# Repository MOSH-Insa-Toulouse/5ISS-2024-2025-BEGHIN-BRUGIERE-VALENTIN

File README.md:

# Gaz Sensor Application

## Introduction
The general objective of this project is to carry out the complete implementation of a gas sensor, from its manufacture, through its integration on a PCB, to its use in a concrete IoT application. This course gives us the opportunity to put our skills into practice at every stage in the design and development of a project. In particular, it covers the main phases such as hardware design, software design and product integration. Various digital tools were used, including KiCad for PCB design, LTSpice for analogue simulations and the Arduino platform for programming.

The application developed detects carbon monoxide and alerts you if critical thresholds are exceeded. Three LEDs indicate the alert levels: green for a safe level, orange for a high level and red for a dangerous level requiring evacuation. An OLED screen, connected via I2C, displays CO levels in real time to check the accuracy of the measurements. These measurements are then sent via a LoRa antenna and retrieved using the NodeRed software, which displays them.

This Git file and the following document contain the steps required to design our application, as well as the results obtained.

## LoRa Antenna
As mentioned above, the aim is to send the data measured by the sensor via a LoRa antenna. To do this, we used the open-source LoRaWAN Network Server ChirpStack, on which we created our application and generated its identifier and access key. Via this server, it is possible to connect to the GEI's main LoRa antenna and view the data stream sent to it.

On the programming side, we used the LoRa RN2483. This module has the advantage of communicating via the UART, so it was easy to connect it to the Arduino and have it send and receive data. We then had to reset and configure the RN2483 microchip according to the identifiers created on ChirpStack. Once this was done, we launched the connection tests and were able to check that our antenna was indeed connected to the main antenna via ChirpStack.

## Components Integration
### OLED Screen
As already mentioned, the OLED screen displays the carbon monoxide level measured by the sensor. The display is of the SSD1306 type and communicates via the I2C bus. We were therefore able to integrate it easily into our system, in particular by using adafruit libraries. By configuring the screen display, i.e. the size, colour and position of the text, we were able to display our first tests on the screen. We also used this screen as a test indicator to check the veracity and accuracy of the measurements taken by the sensor.
### Gaz Sensor
Adding the gas sensor to the application was not so easy. We had trouble understanding how the sensor worked and how to retrieve the measurements. However, after a bit of research we managed to get it to work properly.

This sensor detects the presence of carbon monoxide by a variation in resistance. First of all, the sensor has to be allowed to heat up in order to obtain values in line with reality, and then to adapt to its environment. The resistance value is recovered via a serial link and processed to obtain a usable level in ppm. We were then able to display on the screen the measurements taken in real time by the sensor.
### LEDs
To implement a visual alert, we decided to use three different coloured LEDs to symbolise our alert levels. The first level, green, means that the level of CO measured by the sensor is not toxic. The second, orange, symbolises that the quantity of gas is high and that exposure for too long can cause headaches. Finally, the red alert level lights up when the level of monoxide is above the safety threshold. Time to leave the room. We found the three thresholds in the literature on the websites of health bodies to reflect reality. The LEDs were switched on via a condition loop when the sensor measurements were retrieved.

## Node-RED Application
After that, we implemented Node-RED to visualise the data collected by the sensor. The idea was for the sensor readings transmitted via the LoRa antenna and processed by Chirpstack to be retrieved by Node-RED and displayed using its dashboard functionality. Using the MQTT protocol, we subscribed Node-RED to a Chirpstack topic in which it published the sensor measurements. This enabled us to retrieve the data transmitted on the LoRa network. The values were then displayed by creating a simple but powerful interface for viewing the gas sensor data in real time. 

For more information, read the Node-RED report [here](Rapport_NodeRed).

## The electrical circuit
Here is the complete electrical diagram of our system. It consists of the Arduino UNO shield, the three LEDs, the gas sensor, the OLED screen and an amplifier.

The gas sensor produced has a very high resistance which varies according to the type and presence of gas. Its resistance is of the order of gigohms, which implies an extremely low current of the order of nanoampere (nA) flowing to the ADC. Using an Arduino with a 10-bit ADC requires the signal leaving the gas sensor to be amplified. We therefore designed an amplification circuit based on an operational amplifier and simulated it using LTSpice. To find out more, read the LT-Spice report [here](Rapport_LTSpice).

## PCB Design
The PCB was designed using KiCad software. Starting with the previous electrical circuit, the components had to be placed on the Arduino UNO shield and then routed. This was a complex process because we had a lot of components that were quite imposing in terms of space, which did not make placement easy. The final aim was, instead of using a breadboard, to have all the components needed for our application on a single board. The OLED screen and the connectors for the LoRa module have been placed on the other side of the shield so that they can be accessed. Here is the final PCB for our project.

Below, there is a 3D view of the PCB after conception.

-- Front view:

--Back view:

## Conclusion
The next stage of our project is to print the PCB and then solder the components. Finally, we will have to test our application by uploading our code onto the board. 

The overall objective of this module is to carry out the complete implementation of a gas sensor, from its manufacture, through its integration on a PCB, to its use in a concrete IoT application. This course thus gives us the opportunity to put our skills into practice at every stage of the design and development of a project. In particular, it covers the main phases such as hardware design, software design and product integration. 

In terms of energy consumption, we should look at the consumption of each component. If it is too high, we will have to switch to other components that consume less energy.

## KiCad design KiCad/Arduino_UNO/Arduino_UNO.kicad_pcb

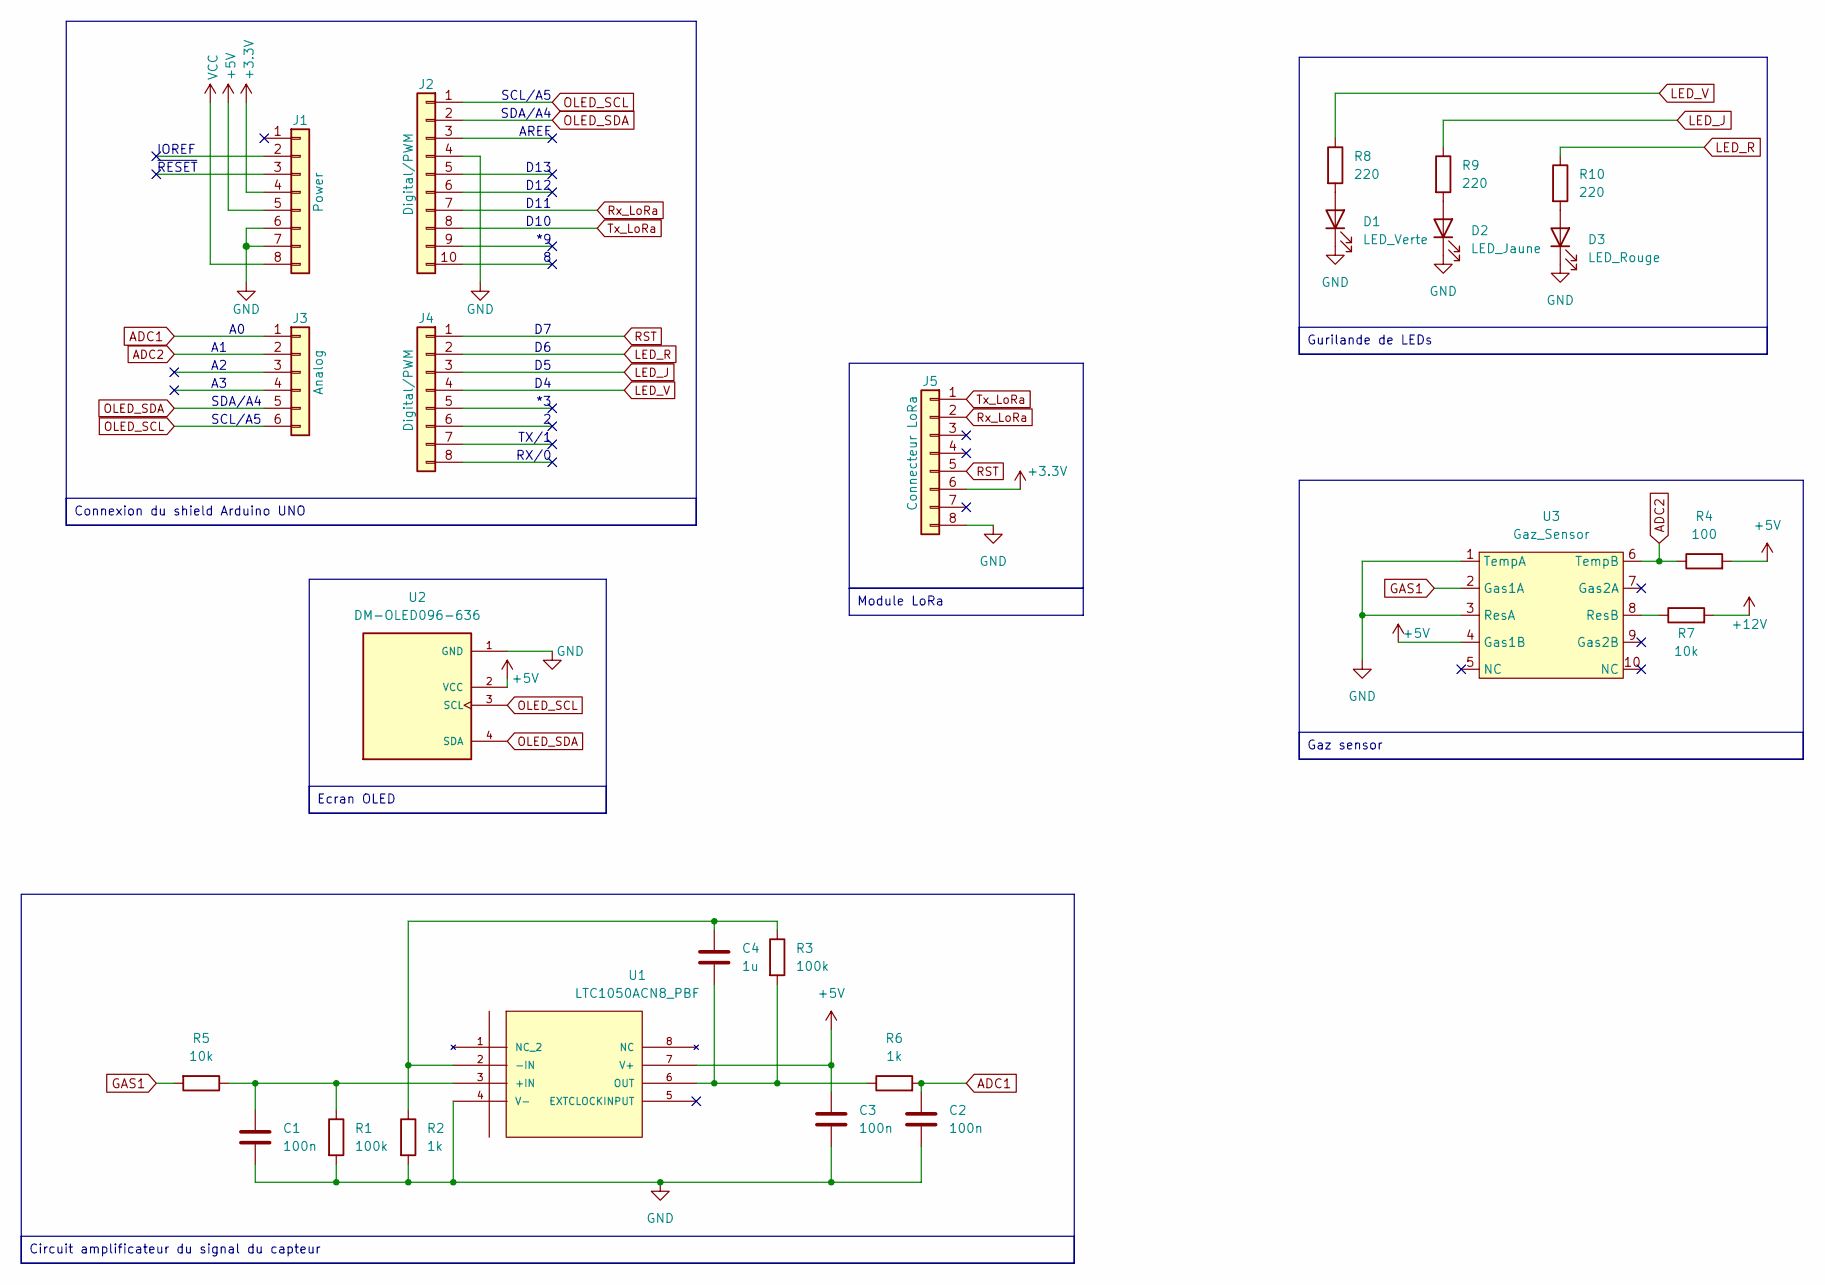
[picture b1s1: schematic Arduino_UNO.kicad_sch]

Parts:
C1, C2, C3: 100n; C_Disc_D5.1mm_W3.2mm_P5.00mm
C4: 1u; C_Rect_L7.5mm_W6.5mm_P5.00mm
D1: LED_Verte; LED_D3.0mm
D2: LED_Jaune; LED_D3.0mm
D3: LED_Rouge; LED_D3.0mm
J1: Power; PinSocket_1x08_P2.54mm_Vertical
J2: Digital/PWM; PinSocket_1x10_P2.54mm_Vertical
J3: Analog; PinSocket_1x06_P2.54mm_Vertical
J4: Digital/PWM; PinSocket_1x08_P2.54mm_Vertical
J5: Connecteur LoRa; PinSocket_1x08_P2.54mm_Vertical
R1, R3: 100k; R_Axial_DIN0207_L6.3mm_D2.5mm_P10.16mm_Horizontal
R2, R6: 1k; R_Axial_DIN0207_L6.3mm_D2.5mm_P10.16mm_Horizontal
R4: 100; R_Axial_DIN0207_L6.3mm_D2.5mm_P10.16mm_Horizontal
R5, R7: 10k; R_Axial_DIN0207_L6.3mm_D2.5mm_P10.16mm_Horizontal
R8, R9, R10: 220; R_Axial_DIN0207_L6.3mm_D2.5mm_P10.16mm_Horizontal
U1: LTC1050ACN8_PBF; DIP-8_W7.62mm; MANUFACTURER_PART_NUMBER ltc1050acn8
U2: DM-OLED096-636; MODULE_DM-OLED096-636; PARTREV 2018-09-10
U3: Gaz_Sensor; TO-5-10_Window

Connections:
+5V: C3.1, J1.5, R4.2, U1.7 (V+), U2.2 (VCC), U3.4 (Gas1B)
+12V: R7.2
ADC1: C2.1, J3.1, R6.2
ADC2: J3.2, R4.1, U3.6 (TempB)
GAS1: R5.2, U3.2 (Gas1A)
GND: C1.2, C2.2, C3.2, D1.1 (K), D2.1 (K), D3.1 (K), J1.6, J1.7, J2.4, J5.8, R1.2, R2.2, U1.4 (V-), U2.1 (GND), U3.1 (TempA), U3.3 (ResA)
LED_J: J4.3, R9.1
LED_R: J4.2, R10.1
LED_V: J4.4, R8.1
unnamed: D1.2 (A), R8.2
unnamed: D2.2 (A), R9.2
unnamed: D3.2 (A), R10.2
unnamed: C1.1, R1.1, R5.1, U1.3 (+IN)
unnamed: C4.1, R2.1, R3.1, U1.2 (-IN)
unnamed: C4.2, R3.2, R6.1, U1.6 (OUT)
unnamed: R7.1, U3.8 (ResB)
OLED_SCL: J2.1, J3.6, U2.3 (SCL)
OLED_SDA: J2.2, J3.5, U2.4 (SDA)
RST: J4.1, J5.5
Rx_LoRa: J2.7, J5.2
Tx_LoRa: J2.8, J5.1
VCC: J1.8

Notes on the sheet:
Gaz sensor
Gurilande de LEDs
Connexion du shield Arduino UNO
Module LoRa
Circuit amplificateur du signal du capteur
Ecran OLED
AREF
SCL/A5
TX/1
D13
~{RESET}
D12
D10
SDA/A4
RX/0
IOREF
D11

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
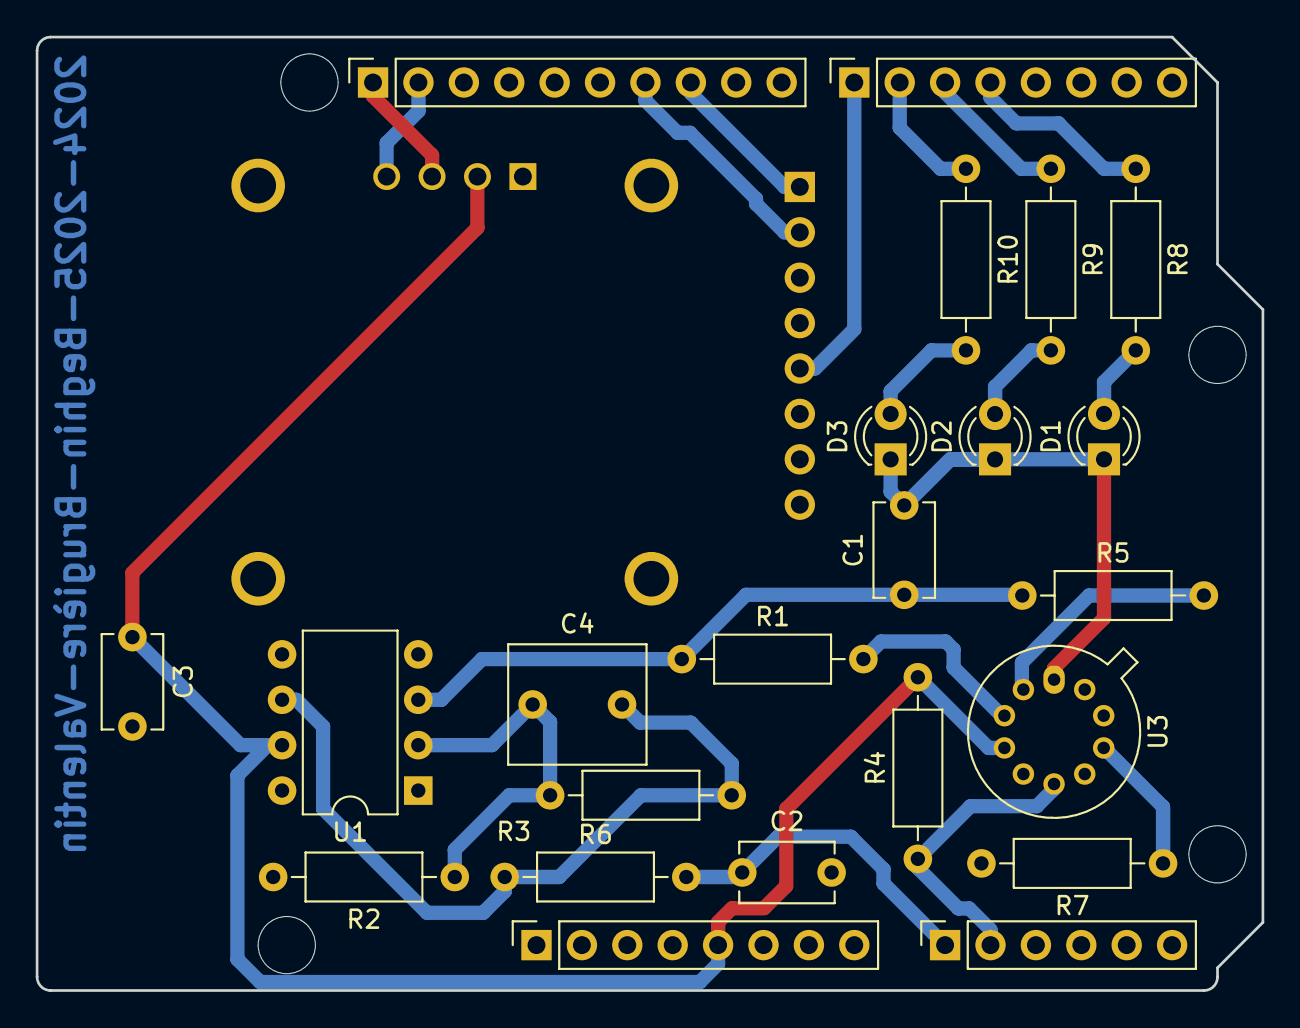
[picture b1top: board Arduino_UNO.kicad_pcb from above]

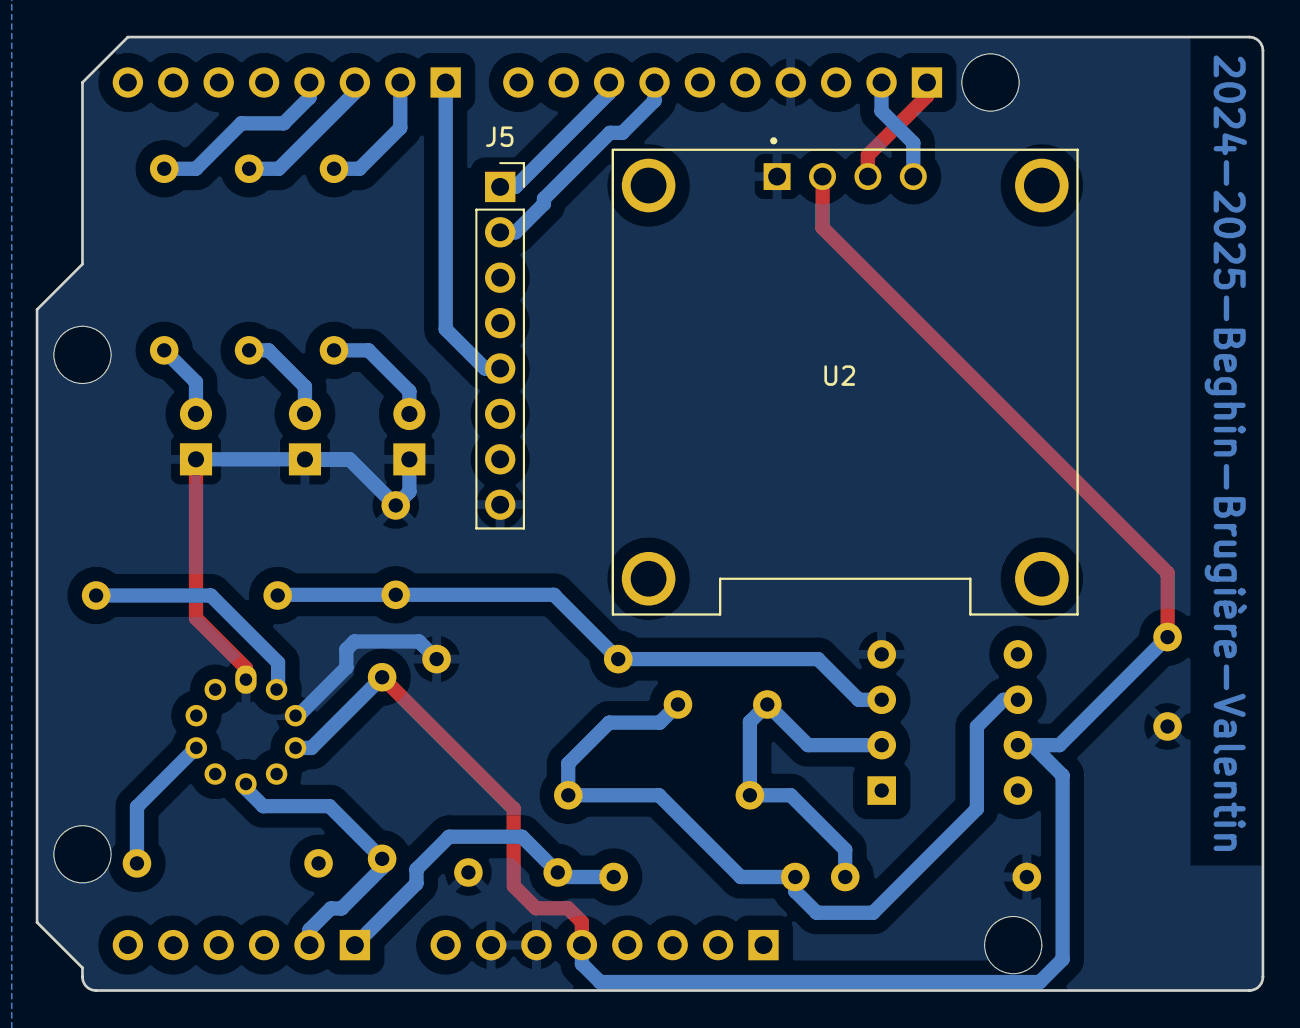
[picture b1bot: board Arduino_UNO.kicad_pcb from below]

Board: 2 copper layers, 68.6 x 53.3 mm, 29 parts (2 on the bottom side), 20 nets.

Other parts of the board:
MH1, MH2, MH3, MH4: MountingHole_3.2mm

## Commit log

2024-12-18 pistes bleues et vertes
2024-12-18 ajout rapport LTspice
2024-12-18 rajoutprojet rapport nodered
2025-01-04 Update README.md
    début
2025-01-06 kicad files
2025-01-09 Create DataSheet
2025-01-09 Update README.md
    lien
2025-01-15 ajout images nodered
2025-01-15 Rename Capture d’écran du 2025-01-15 08-20-30.png to Flow_Nodered
2025-01-15 Rename Flow_Nodered to Flow_Nodered.png
2025-01-15 Rename Capture d’écran du 2025-01-15 08-37-28.png to Application.png
2025-01-15 Rename Capture d’écran du 2025-01-15 08-21-01.png to DecodeurJSON.png
2025-01-15 Rename Capture d’écran du 2025-01-15 08-21-25.png to ConfigMQTTTopic.png
2025-01-15 Rename Capture d’écran du 2025-01-15 08-21-52.png to ConfigServer.png

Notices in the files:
parts and their libraries:
COPYRIGHT: Copyright C 2016 Accelerated Designs. All rights reserved
